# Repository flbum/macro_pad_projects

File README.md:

# Macro Pad Projects

This repository contains a collection of custom macro pads and keyboards built using QMK firmware. These are personal projects ranging from simple macro pads to more complex split keyboards.

## Projects Included

- **bum_deck**: A compact macro pad with custom key mappings.
- **champ_deck**: Another macro pad design with unique features.
- **leroy**: A hand-wired 8-key macro pad with 2 rotary encoders.
- **sh17**: A 17-key numpad-style macro pad, handwired.
- **sh6r2**: A smaller macro pad project.
- **split_keebs**: Split keyboard designs, including the bum_36 split keyboard.

## Getting Started

To build any of these keyboards, you'll need to set up a QMK development environment. Follow the [QMK setup guide](https://docs.qmk.fm/#/getting_started_build_tools).

Each keyboard has its own directory with configuration files. Navigate to the keyboard's folder and use QMK commands like:

```
qmk compile -kb <keyboard_name> -km default
```

For flashing, use:

```
qmk flash -kb <keyboard_name> -km default
```

## Contributing

Feel free to fork and modify these designs. If you have improvements or questions, open an issue or pull request.

## License

This project is licensed under the GNU General Public License v2.0 - see the [LICENSE](LICENSE) file for details.

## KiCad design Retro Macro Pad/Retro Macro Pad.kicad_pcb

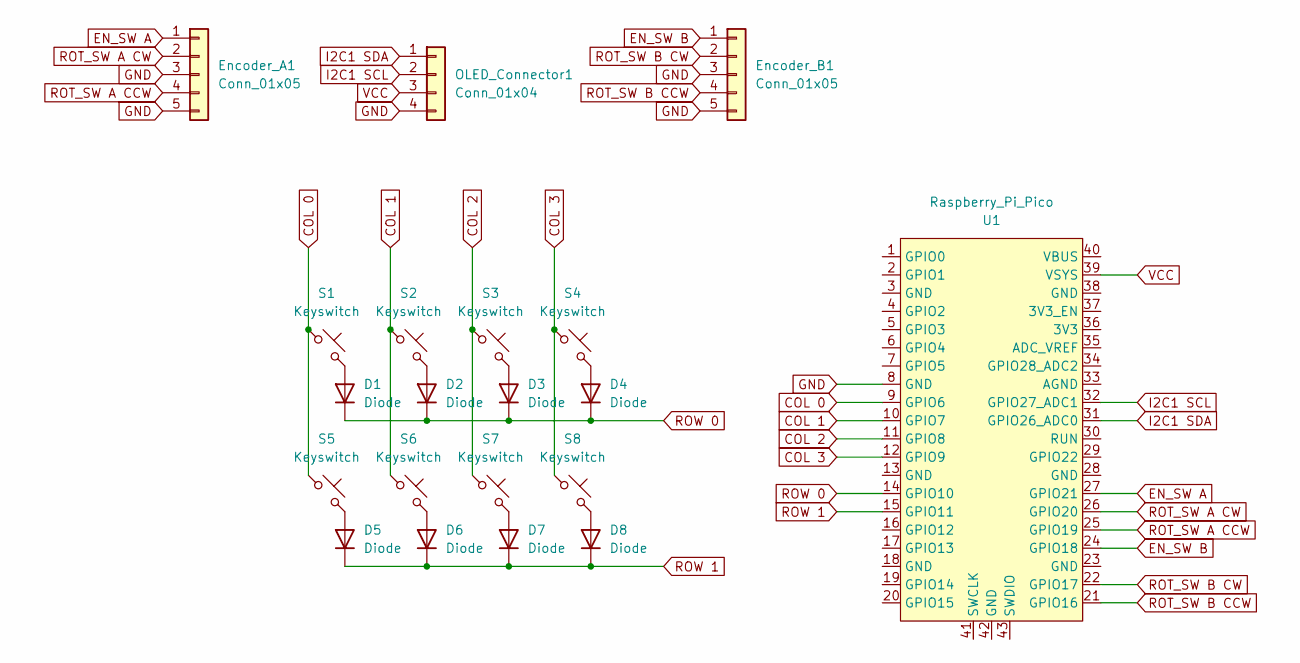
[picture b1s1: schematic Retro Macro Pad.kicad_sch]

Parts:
D1, D2, D3, D4, D5, D6, D7, D8: Diode; Diode_DO-35
Encoder_A1: Conn_01x05; PinHeader_1x05_P2.54mm_Vertical
Encoder_B1: Conn_01x05; PinHeader_1x05_P2.54mm_Vertical
OLED_Connector1: Conn_01x04; PinHeader_1x04_P2.54mm_Vertical
S1, S2, S3, S4, S5, S6, S7, S8: Keyswitch; MX_PCB_1.00u
U1: Raspberry_Pi_Pico

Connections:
COL 0: S1.1, S5.1, U1.9 (GPIO6)
COL 1: S2.1, S6.1, U1.10 (GPIO7)
COL 2: S3.1, S7.1, U1.11 (GPIO8)
COL 3: S4.1, S8.1, U1.12 (GPIO9)
EN_SW A: Encoder_A1.1, U1.27 (GPIO21)
EN_SW B: Encoder_B1.1, U1.24 (GPIO18)
GND: Encoder_A1.3, Encoder_A1.5, Encoder_B1.3, Encoder_B1.5, OLED_Connector1.4, U1.8 (GND)
I2C1 SCL: OLED_Connector1.2, U1.32 (GPIO27_ADC1)
I2C1 SDA: OLED_Connector1.1, U1.31 (GPIO26_ADC0)
unnamed: D1.2 (A), S1.2
unnamed: D2.2 (A), S2.2
unnamed: D3.2 (A), S3.2
unnamed: D4.2 (A), S4.2
unnamed: D5.2 (A), S5.2
unnamed: D6.2 (A), S6.2
unnamed: D7.2 (A), S7.2
unnamed: D8.2 (A), S8.2
ROT_SW A CCW: Encoder_A1.4, U1.25 (GPIO19)
ROT_SW A CW: Encoder_A1.2, U1.26 (GPIO20)
ROT_SW B CCW: Encoder_B1.4, U1.21 (GPIO16)
ROT_SW B CW: Encoder_B1.2, U1.22 (GPIO17)
ROW 0: D1.1 (K), D2.1 (K), D3.1 (K), D4.1 (K), U1.14 (GPIO10)
ROW 1: D5.1 (K), D6.1 (K), D7.1 (K), D8.1 (K), U1.15 (GPIO11)
VCC: OLED_Connector1.3, U1.39 (VSYS)

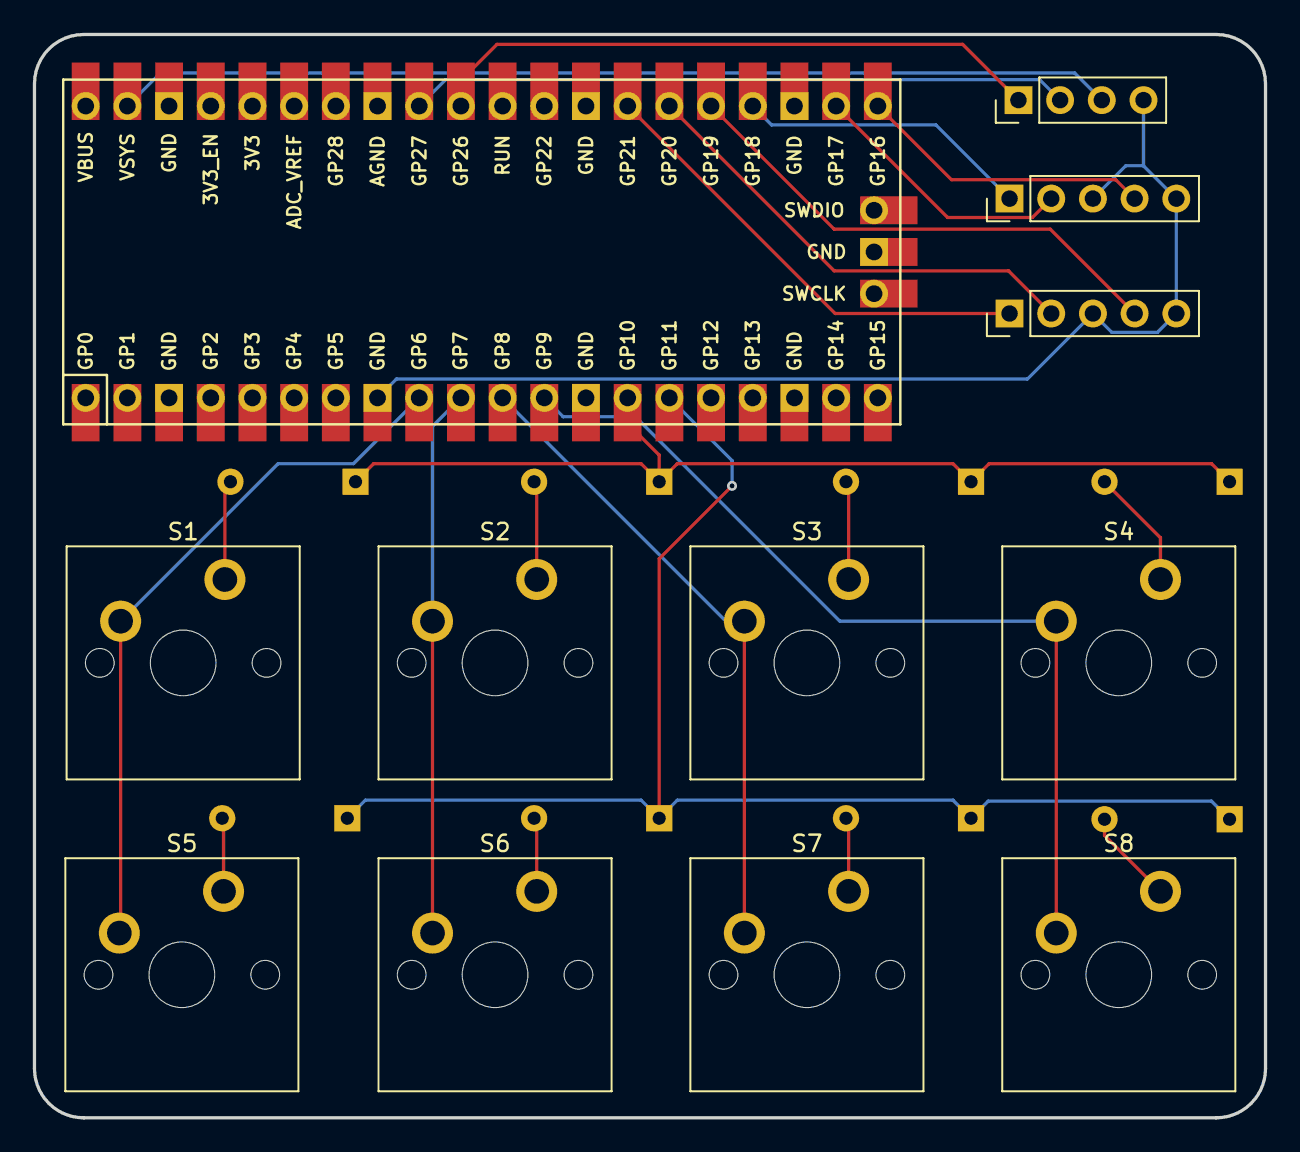
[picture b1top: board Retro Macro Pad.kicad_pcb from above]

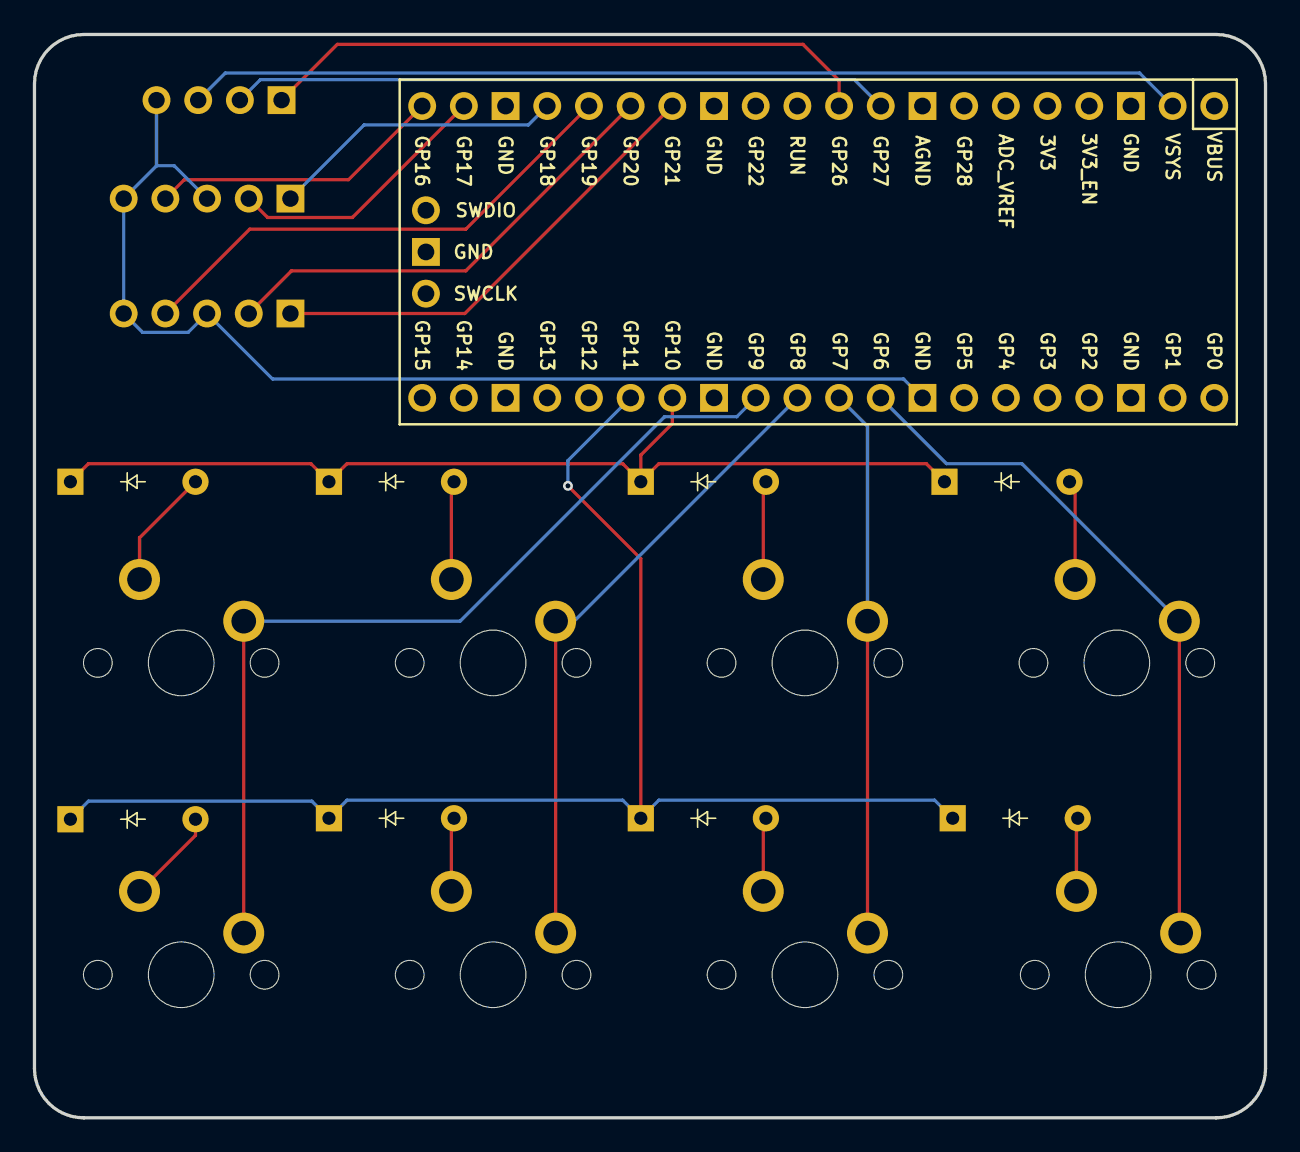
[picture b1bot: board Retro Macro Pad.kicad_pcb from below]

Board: 2 copper layers, 75.0 x 66.0 mm, 20 parts (8 on the bottom side), 24 nets.

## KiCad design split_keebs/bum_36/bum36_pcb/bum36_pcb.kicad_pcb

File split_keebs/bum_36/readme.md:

# bum_36

A compact hand-wired split keyboard with 36 keys, dual rotary encoders, 3D-printed plates/cases, and QMK/Vial firmware support.

## Overview

The `bum_36` is a small split ergonomic keyboard built around a hand-wired matrix and Pro Micro-compatible controllers. This project directory includes the printable case files, build photos, and firmware needed to reproduce or customize the board.

## Gallery

| Top View | Front View |q
| --- | --- |
|  |  |

| Wiring | Connection Detail |
| --- | --- |
|  |  |

## Project Files

### STL files

- `stl_files/left_plate_v1.1.stl`
- `stl_files/left_plate_v1.2.stl`
- `stl_files/right_plate_v1.2.stl`
- `stl_files/right_case_v1.1.stl`

### Firmware

- `firmware/` - local copy of the keyboard firmware files
- `firmware/keymaps/vial/` - Vial-enabled keymap
- `bum_36_vial.hex` - prebuilt firmware image for flashing

If you are integrating this into a QMK tree, the matching keyboard files are also available under `qmk_firmware/keyboards/bum_36/`.

## Keyboard Specs

- Layout: 36-key split layout
- Construction: hand-wired
- Firmware: QMK with Vial keymap included
- Controllers: Pro Micro-compatible
- Rotary encoders: 2
- Split communication: I2C

## Materials

This build used the actual parts and wiring for the bum_36 split keyboard.

### Core electronics

- Controllers: 2 Arduino Pro Micros
- Switches: 36 Cherry MX Brown switches
- Diodes: 1N4148 diodes
- Rotary encoders: 2 standard CY1111/EC11-style encoders
- Split communication: 4-pin USB-C breakout boards used to pass I2C between halves

### Printed parts

- Plate material: 3D-printed plastic
- Case material: 3D-printed plastic
- Print profile: standard hobby printer settings with enough strength for the plates and case
- STL version used: the included `stl_files/` versions in this folder

### Hardware and consumables

- Matrix wiring: solid copper wire for rows and columns
- Board wiring: stranded wire for the connections to the Pro Micros and other components
- Solder: 70/30 solder
- Heat shrink: clear shrink tubing for insulation
- USB: USB-C cable and a 4-pin USB-C breakout for I2C communication
- Keycaps: standard keycaps and rotary encoder knobs
## Build Notes

### Design summary

This board uses a compact split layout with thumb keys and one encoder per half. The included files suggest a hand-wired build paired with 3D-printed structural parts.

### Assembly summary

1. Print the selected plate and case files.
2. Install switches and encoders into the printed parts.
3. Hand-wire the switch matrix and diodes.
4. Wire each half to its controller.
5. Connect the two halves using the chosen split communication hardware.
6. Flash the firmware and verify matrix, layers, and encoder behavior.

## Firmware

The repository includes firmware sources and a precompiled Vial `.hex` file.

### Default layer behavior

- Base layer: alphas and primary typing layout
- Lower layer: numbers and navigation
- Raise layer: symbols and function keys
- Adjust layer: boot/reset and media controls

### Encoder behavior

- Base: mouse wheel on one encoder, volume on the other
- Lower: horizontal navigation and media track control
- Raise: arrow-style movement and display brightness
- Adjust: navigation and volume control

### QMK build example

```sh
make bum_36:default
```

### Flash example

```sh
make bum_36:default:flash
```

For QMK setup instructions, see the official documentation: <https://docs.qmk.fm/>.

## Repository Structure

```text
split_keebs/bum_36/
├── images/
├── stl_files/
├── firmware/
├── bum_36_vial.hex
└── readme.md
```

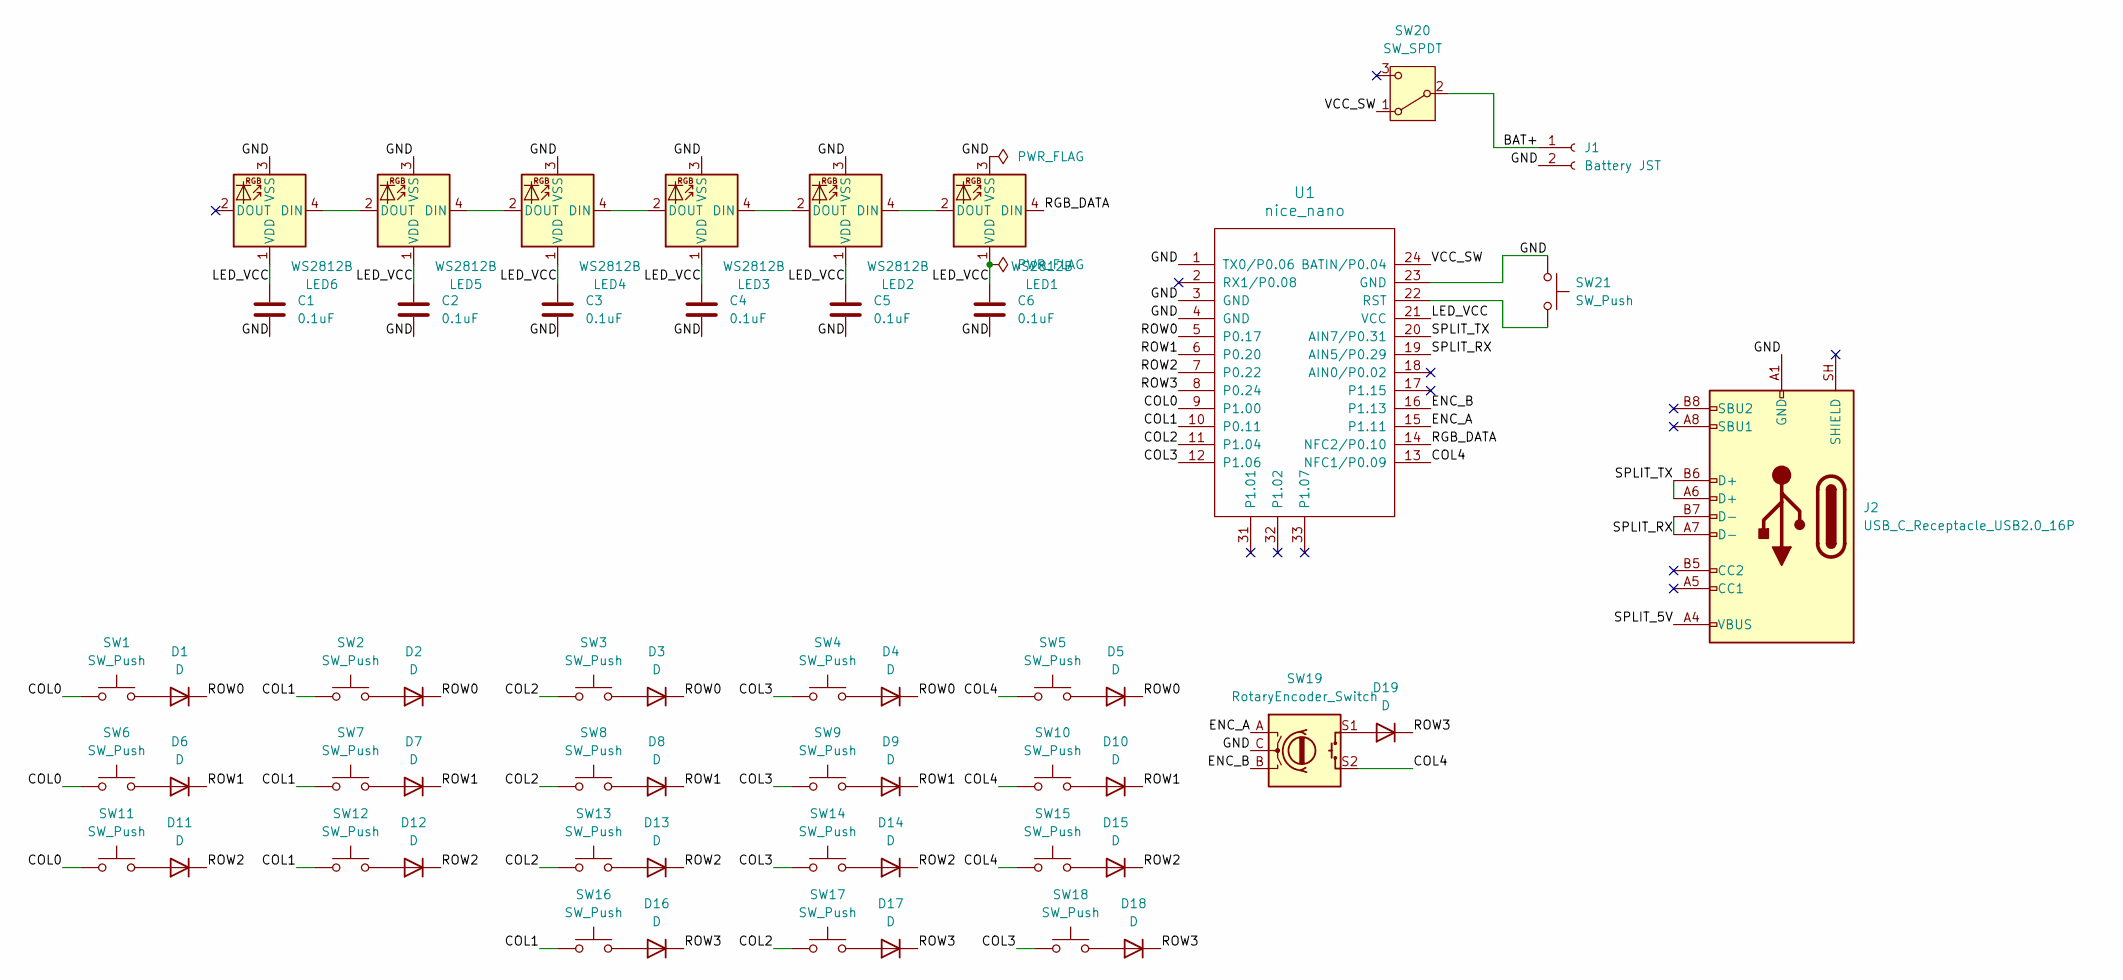
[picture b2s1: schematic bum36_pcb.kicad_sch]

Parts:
C1, C2, C3, C4, C5, C6: 0.1uF; C_0805_2012Metric
D1, D2, D3, D4, D5, D6, D7, D8, D9, D10, D11, D12, D13, D14, D15, D16, D17, D18, D19: D; D_SOD-123
J1: Battery JST; JST_PH_B2B-PH-K_1x02_P2.00mm_Vertical
J2: USB_C_Receptacle_USB2.0_16P; USB_C_Receptacle_HRO_TYPE-C-31-M-12
LED1, LED2, LED3, LED4, LED5, LED6: WS2812B; LED_WS2812B_PLCC4_5.0x5.0mm_P3.2mm
SW1, SW2, SW3, SW4, SW5, SW6, SW7, SW8, SW9, SW10, SW11, SW12, SW13, SW14, SW15, SW16, SW17, SW18: SW_Push; SW_Cherry_MX_1.00u_PCB
SW19: RotaryEncoder_Switch; RotaryEncoder_Alps_EC11E-Switch_Vertical_H20mm
SW20: SW_SPDT; SW_SPDT_Shouhan_MSK12C02
SW21: SW_Push; SW_SPST_SKQG_WithoutStem
U1: nice_nano

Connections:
/BAT+: J1.1, SW20.2 (B)
/COL0: SW1.1, SW6.1, SW11.1, U1.9 (P1.00)
/COL1: SW2.1, SW7.1, SW12.1, SW16.1, U1.10 (P0.11)
/COL2: SW3.1, SW8.1, SW13.1, SW17.1, U1.11 (P1.04)
/COL3: SW4.1, SW9.1, SW14.1, SW18.1, U1.12 (P1.06)
/COL4: SW5.1, SW10.1, SW15.1, SW19.S2, U1.13 (NFC1/P0.09)
/ENC_A: SW19.A, U1.15 (P1.11)
/ENC_B: SW19.B, U1.16 (P1.13)
/GND: C1.2, C2.2, C3.2, C4.2, C5.2, C6.2, J1.2, J2.A1 (GND), J2.A12 (GND), J2.B1 (GND), J2.B12 (GND), LED1.3 (VSS), LED2.3 (VSS), LED3.3 (VSS), LED4.3 (VSS), LED5.3 (VSS), LED6.3 (VSS), SW19.C, SW21.1, U1.1 (TX0/P0.06), U1.3 (GND), U1.4 (GND), U1.23 (GND)
/LED_VCC: C1.1, C2.1, C3.1, C4.1, C5.1, C6.1, LED1.1 (VDD), LED2.1 (VDD), LED3.1 (VDD), LED4.1 (VDD), LED5.1 (VDD), LED6.1 (VDD), U1.21 (VCC)
/RGB_DATA: LED1.4 (DIN), U1.14 (NFC2/P0.10)
/ROW0: D1.1 (K), D2.1 (K), D3.1 (K), D4.1 (K), D5.1 (K), U1.5 (P0.17)
/ROW1: D6.1 (K), D7.1 (K), D8.1 (K), D9.1 (K), D10.1 (K), U1.6 (P0.20)
/ROW2: D11.1 (K), D12.1 (K), D13.1 (K), D14.1 (K), D15.1 (K), U1.7 (P0.22)
/ROW3: D16.1 (K), D17.1 (K), D18.1 (K), D19.1 (K), U1.8 (P0.24)
/SPLIT_5V: J2.A4 (VBUS), J2.A9 (VBUS), J2.B4 (VBUS), J2.B9 (VBUS)
/SPLIT_RX: J2.A7 (D-), J2.B7 (D-), U1.19 (AIN5/P0.29)
/SPLIT_TX: J2.A6 (D+), J2.B6 (D+), U1.20 (AIN7/P0.31)
/VCC_SW: SW20.1 (A), U1.24 (BATIN/P0.04)
unnamed: D1.2 (A), SW1.2
unnamed: D2.2 (A), SW2.2
unnamed: D3.2 (A), SW3.2
unnamed: D4.2 (A), SW4.2
unnamed: D5.2 (A), SW5.2
unnamed: D6.2 (A), SW6.2
unnamed: D7.2 (A), SW7.2
unnamed: D8.2 (A), SW8.2
unnamed: D9.2 (A), SW9.2
unnamed: D10.2 (A), SW10.2
unnamed: D11.2 (A), SW11.2
unnamed: D12.2 (A), SW12.2
unnamed: D13.2 (A), SW13.2
unnamed: D14.2 (A), SW14.2
unnamed: D15.2 (A), SW15.2
unnamed: D16.2 (A), SW16.2
unnamed: D17.2 (A), SW17.2
unnamed: D18.2 (A), SW18.2
unnamed: D19.2 (A), SW19.S1
unnamed: LED1.2 (DOUT), LED2.4 (DIN)
unnamed: LED2.2 (DOUT), LED3.4 (DIN)
unnamed: LED3.2 (DOUT), LED4.4 (DIN)
unnamed: LED4.2 (DOUT), LED5.4 (DIN)
unnamed: LED5.2 (DOUT), LED6.4 (DIN)
unnamed: SW21.2, U1.22 (RST)

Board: 2 copper layers, 55 parts (5 on the bottom side), 44 nets, no tracks yet.

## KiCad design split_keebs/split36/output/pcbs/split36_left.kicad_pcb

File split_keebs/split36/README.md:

# split36

This is an in-progress wireless version of the split36 keyboard.

Work is actively ongoing, with PCB layout and footprint placement already started.

More details will be added as the design progresses.

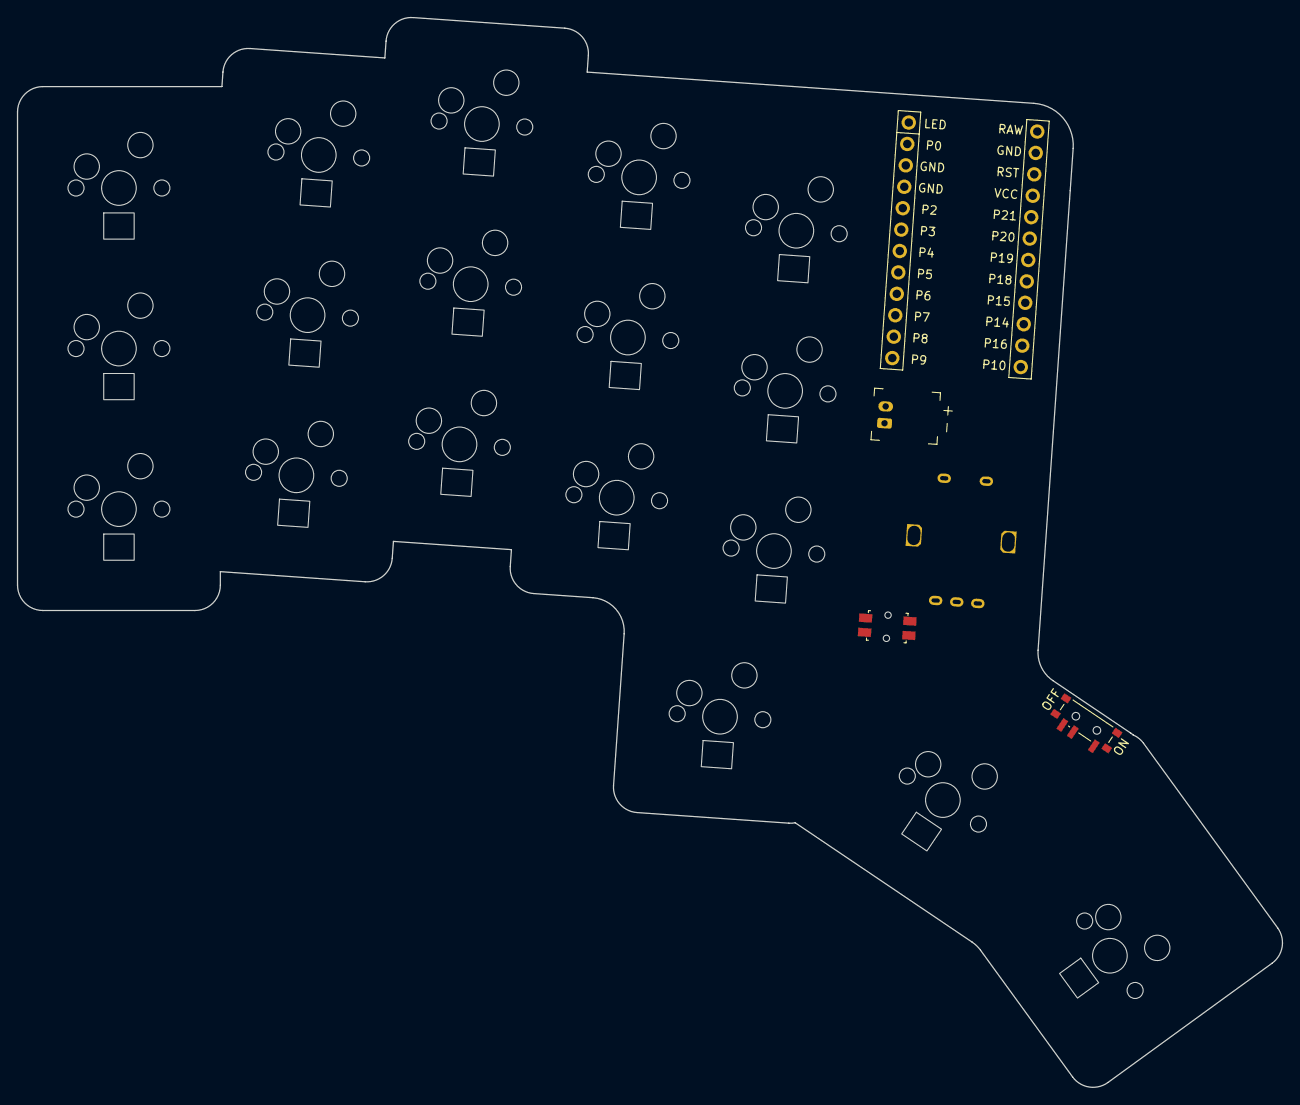
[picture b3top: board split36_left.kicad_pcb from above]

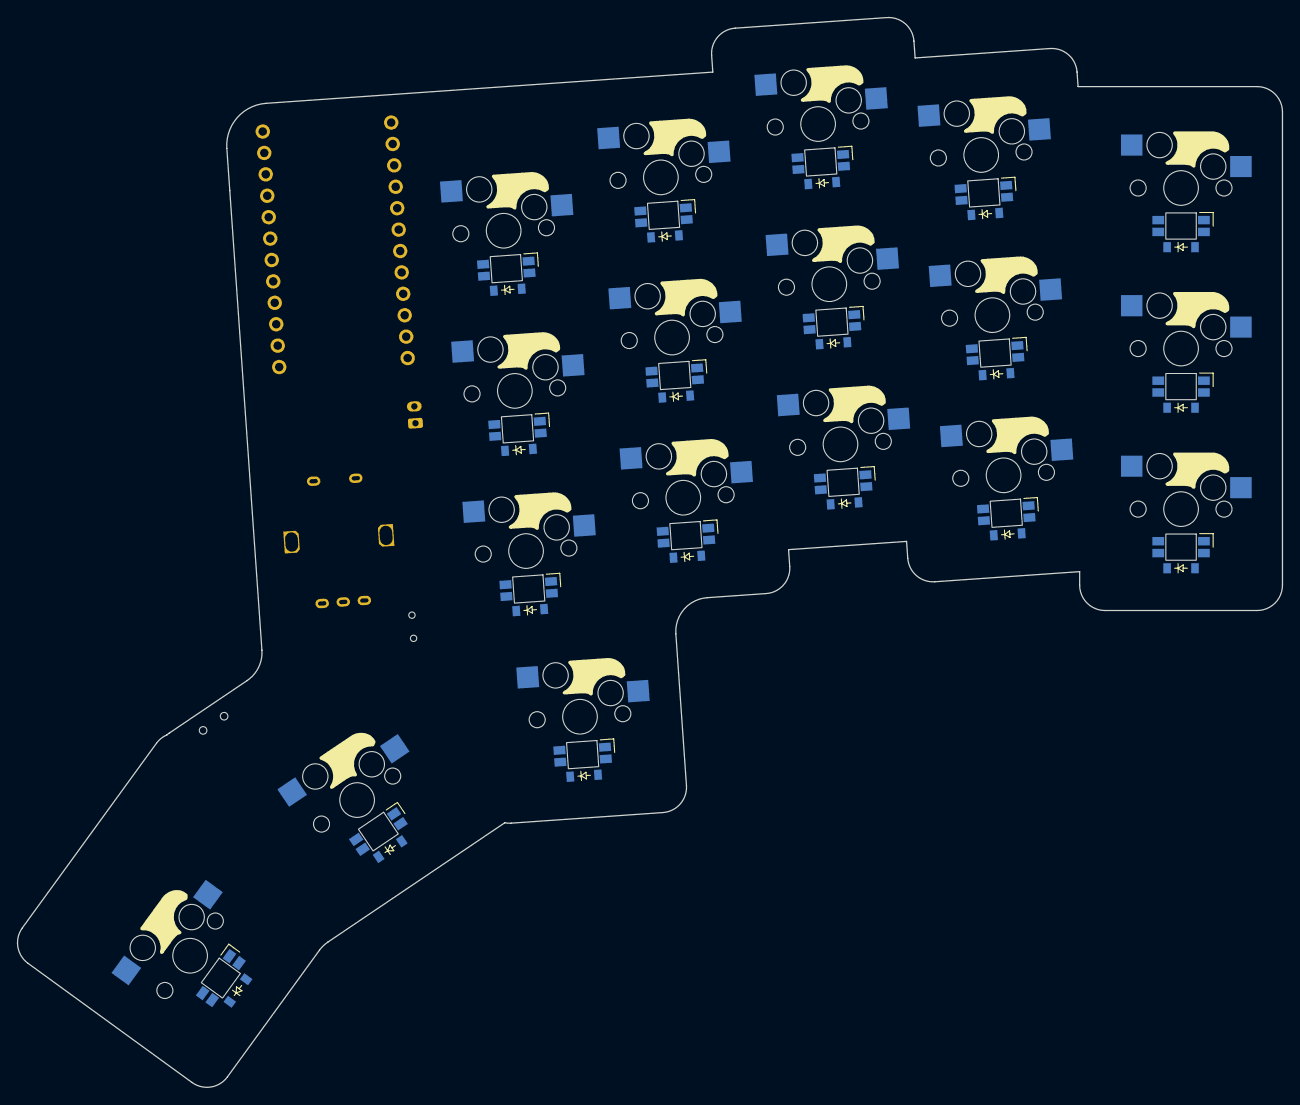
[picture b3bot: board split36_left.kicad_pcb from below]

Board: 2 copper layers, 149.7 x 126.6 mm, 59 parts (54 on the bottom side), 50 nets, no tracks yet.

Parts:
D1, D2, D3, D4, D5, D6, D7, D8, D9, D10, D11, D12, D13, D14, D15, D16, D17, D18: diode_tht_sod123
JST1: battery_connector_jst_ph_2
LED1, LED2, LED3, LED4, LED5, LED6, LED7, LED8, LED9, LED10, LED11, LED12, LED13, LED14, LED15, LED16, LED17, LED18: led_SK6812mini-e (per-keysingle-side)
MCU1: mcu_nice_nano
PWR1: power_switch_smd_side
RE1: rotary_encoder_ec11_ec12
RST1: reset_switch_smd_side
S1, S2, S3, S4, S5, S6, S7, S8, S9, S10, S11, S12, S13, S14, S15, S16, S17, S18: switch_mx

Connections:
BAT_P: JST1.2, PWR1.1
C0: S1.1, S2.1, S3.1, S16.1
C1: S4.1, S5.1, S6.1, S17.1
C2: S7.1, S8.1, S9.1, S18.1
C3: S10.1, S11.1, S12.1
C4: S13.1, S14.1, S15.1
GND: JST1.1, LED1.3, LED2.3, LED3.3, LED4.3, LED5.3, LED6.3, LED7.3, LED8.3, LED9.3, LED10.3, LED11.3, LED12.3, LED13.3, LED14.3, LED15.3, LED16.3, LED17.3, LED18.3, MCU1.2, MCU1.21, MCU1.22, RE1.B, RST1.1, RST1.3
LED: LED3.4, MCU1.24
LED_2: LED3.2, LED6.4
LED_3: LED6.2, LED9.4
LED_4: LED9.2, LED12.4
LED_5: LED12.2, LED15.4
LED_6: LED14.4, LED15.2
LED_7: LED11.4, LED14.2
LED_8: LED8.4, LED11.2
LED_9: LED5.4, LED8.2
LED_10: LED2.4, LED5.2
LED_11: LED1.4, LED2.2
LED_12: LED1.2, LED4.4
LED_13: LED4.2, LED7.4
LED_14: LED7.2, LED10.4
LED_15: LED10.2, LED13.4
LED_16: LED13.2, LED16.4
LED_17: LED16.2, LED17.4
LED_18: LED17.2, LED18.4
R0: D3.1, D6.1, D9.1, D12.1, D15.1
R1: D2.1, D5.1, D8.1, D11.1, D14.1
R2: D1.1, D4.1, D7.1, D10.1, D13.1
R3: D16.1, D17.1, D18.1
RAW: MCU1.1, PWR1.2
RST: MCU1.3, RST1.2, RST1.4
VCC: LED1.1, LED2.1, LED3.1, LED4.1, LED5.1, LED6.1, LED7.1, LED8.1, LED9.1, LED10.1, LED11.1, LED12.1, LED13.1, LED14.1, LED15.1, LED16.1, LED17.1, LED18.1, MCU1.4
far_bottom: D13.2, S13.2
far_home: D14.2, S14.2
far_top: D15.2, S15.2
home_thumb: D17.2, S17.2
index_bottom: D10.2, S10.2
index_home: D11.2, S11.2
index_top: D12.2, S12.2
inner_thumb: D16.2, S16.2
middle_bottom: D7.2, S7.2
middle_home: D8.2, S8.2
middle_top: D9.2, S9.2
outer_thumb: D18.2, S18.2
pinkie_bottom: D1.2, S1.2
pinkie_home: D2.2, S2.2
pinkie_top: D3.2, S3.2
ring_bottom: D4.2, S4.2
ring_home: D5.2, S5.2
ring_top: D6.2, S6.2

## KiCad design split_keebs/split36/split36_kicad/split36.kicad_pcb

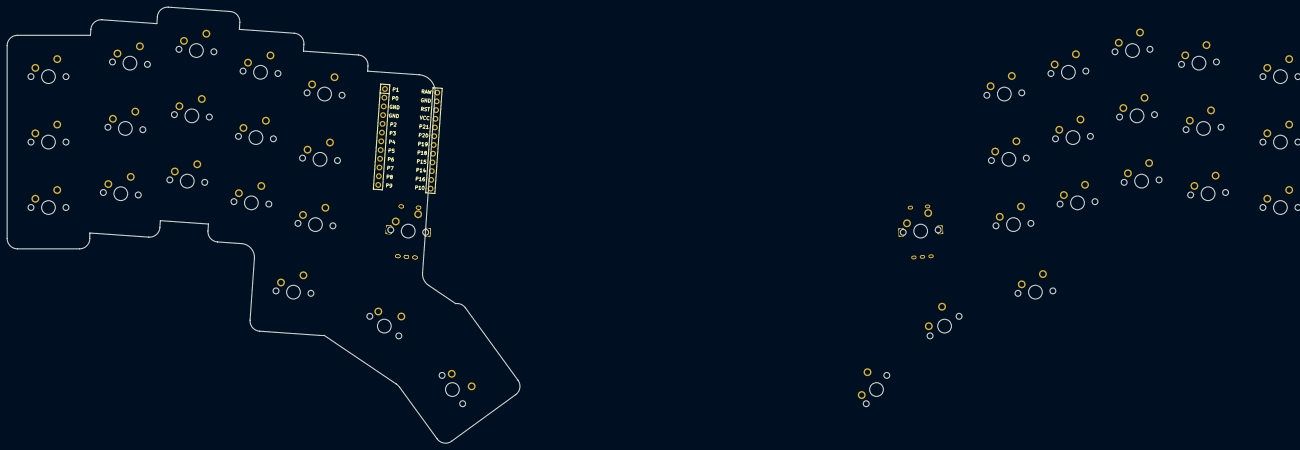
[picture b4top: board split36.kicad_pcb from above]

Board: 2 copper layers, 148.9 x 126.6 mm, 42 parts (0 on the bottom side), 8 nets, no tracks yet.

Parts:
MCU1: mcu_nice_nano
RE1, RE2, RE3: rotary_encoder_ec11_ec12
S1, S2, S3, S4, S5, S6, S7, S8, S9, S10, S11, S12, S13, S14, S15, S16, S17, S18, S19, S20, S21, S22, S23, S24, S25, S26, S27, S28, S29, S30, S31, S32, S33, S34, S35, S36, S37, S38: MX

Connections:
C0: S1.2, S2.2, S3.2, S16.2, S20.2, S21.2, S22.2, S35.2
C1: S4.2, S5.2, S6.2, S17.2, S23.2, S24.2, S25.2, S36.2
C2: S7.2, S8.2, S9.2, S18.2, S26.2, S27.2, S28.2, S37.2
C3: S10.2, S11.2, S12.2, S19.2, S29.2, S30.2, S31.2, S38.2
C4: S13.2, S14.2, S15.2, S32.2, S33.2, S34.2
GND: MCU1.2, MCU1.21, MCU1.22, RE1.B, RE2.B, RE3.B
RE_A: RE1.A, RE2.A, RE3.A
RE_C: RE1.C, RE2.C, RE3.C

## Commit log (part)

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2025-04-10 macos help
2025-04-10 Much needed reconstruction
2025-04-11 organization
2025-04-17 Push it
2025-04-18 on the grind
2025-05-07 Added bum_deck
2026-03-15 Added projects I've been working on
2026-03-15 removed stale projects
2026-03-15 reorganized folder structure bum36
2026-03-16 created bum_36 in qmk
2026-03-16 updated keyboard.json
2026-03-17 modified bum_36 configs
2026-03-17 Create qmk_firmware
2026-03-21 updated bum_36
2026-03-24 woking board setup
2026-03-24 Update qmk_firmware
2026-03-27 created gitignore
2026-03-29 updated bum36 repo
2026-03-29 removed excess stls
2026-03-29 removed
2026-03-29 rename to firmware folder
2026-03-29 included hex
2026-04-02 updated keymaps
2026-04-06 added temp image
2026-04-06 added images and updated readme
2026-04-06 Added split36 to split_keebs
2026-04-06 Added split36
2026-04-06 Add split36 to macro_pad_projects
2026-04-06 Cleaned up repo
2026-04-08 Reconstructed repo for pulic use
2026-04-08 Add leroy project to macro_pad_projects repo
2026-04-08 Added leroy
2026-04-08 Clean up and standardize repo for public release: remove build artifacts, update docs, add licenses, standardize README naming
2026-06-01 case updates
2026-06-13 created velociraptor36
